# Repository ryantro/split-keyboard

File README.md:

# split-keyboard

I chose this as my project for [ECE 561 - Hardware/Software Design of Embedded Systems](https://www.online.colostate.edu/courses/ECE/ECE561.dot)

The project is a split mechanical keyboard built from scratch (and a microprocessor development board).

The noteable features:
- Split halves: Communicate via an I2C bus. The left half is the master device and the left half is the slave device.
- Profile selection: Special keys change the profile of the keyboard, changing the functions of certain keys and the joystick.
- LCD screen: Indicates the currently active profile.
- Joystick: Can act as either a mouse or a joystick depending on profile.

# Tools

### KiCAD

Schematic and PCB layout designed in KiCAD.

PCBs ordered from [https://www.pcbway.com/](https://www.pcbway.com/)

### Teensyduino

Firmware written in Teensyduino IDE.

# Refrences

[https://github.com/ruiqimao/keyboard-pcb-guide](https://github.com/ruiqimao/keyboard-pcb-guide)

[https://www.pjrc.com/teensy/teensyduino.html](https://www.pjrc.com/teensy/teensyduino.html)

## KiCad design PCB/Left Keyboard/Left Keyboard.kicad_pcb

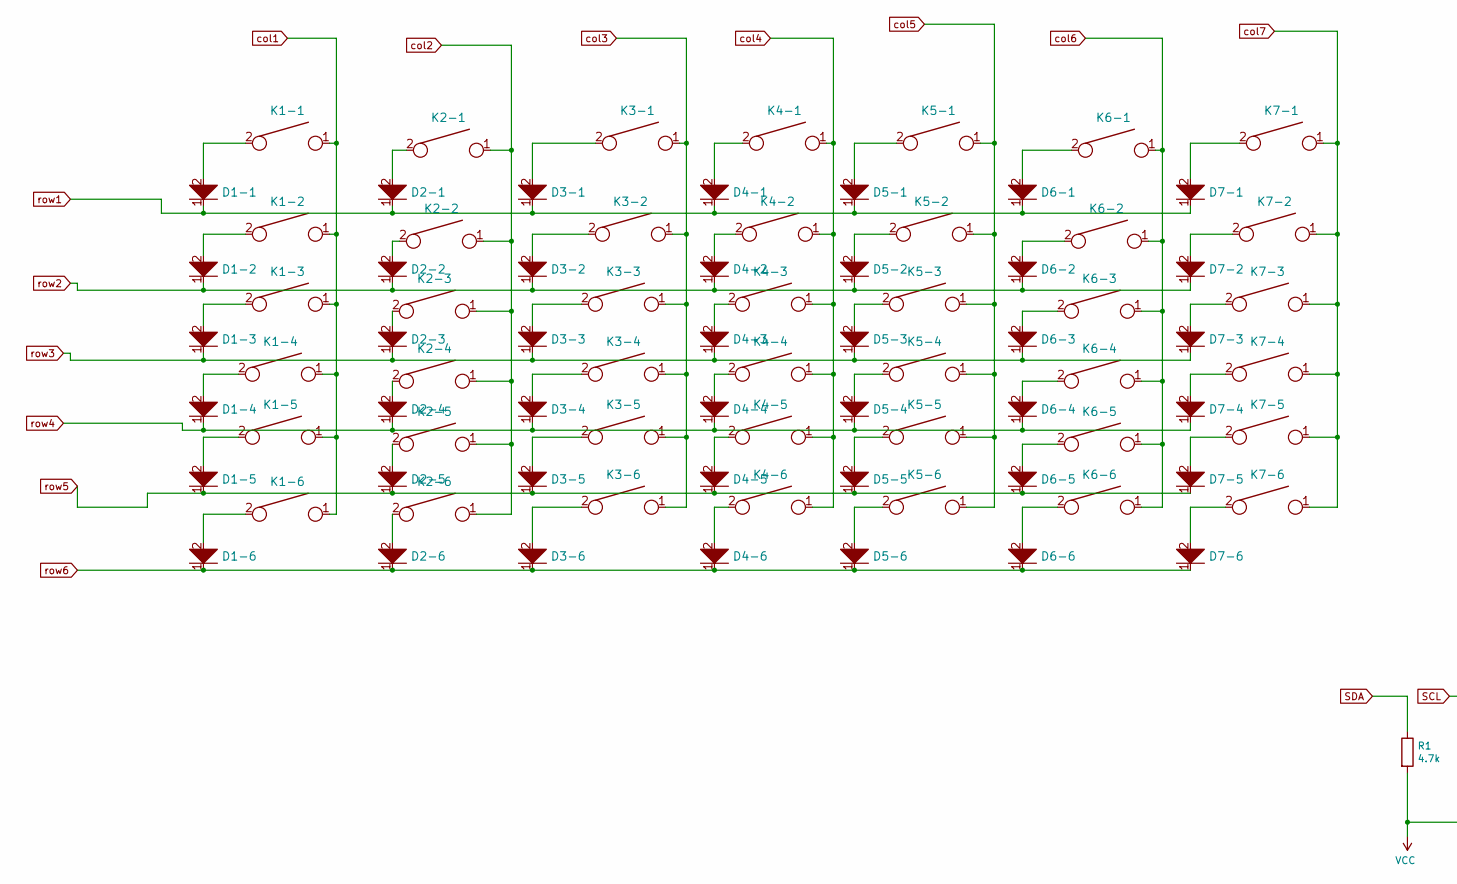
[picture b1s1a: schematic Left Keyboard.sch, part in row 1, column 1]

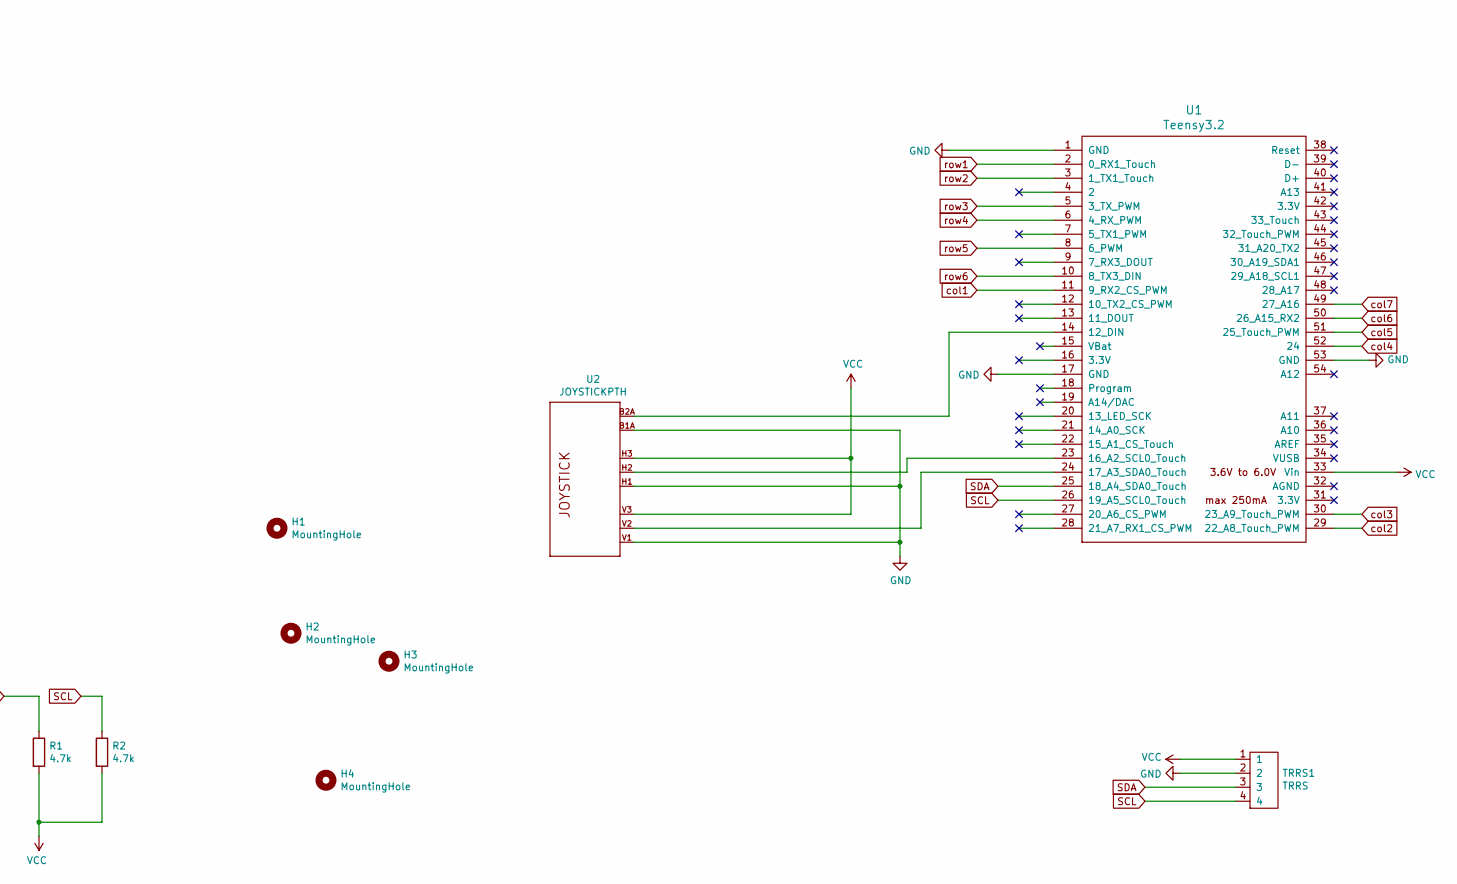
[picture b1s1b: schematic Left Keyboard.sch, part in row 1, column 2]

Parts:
D1-1, D1-2, D1-3, D1-4, D1-5, D1-6, D2-1, D2-2, D2-3, D2-4, D2-5, D2-6, D3-1, D3-2, D3-3, D3-4, D3-5, D3-6, D4-1, D4-2, D4-3, D4-4, D4-5, D4-6, D5-1, D5-2, D5-3, D5-4, D5-5, D5-6, D6-1, D6-2, D6-3, D6-4, D6-5, D6-6, D7-1, D7-2, D7-3, D7-4, D7-5, D7-6: D; D_axial
H1, H2, H3, H4: MountingHole; MountingHole_2.7mm_M2.5_Pad
K1-1, K1-2, K1-3, K1-4, K1-5, K1-6, K2-1, K2-2, K2-3, K2-4, K2-5, K2-6, K3-1, K3-2, K3-3, K3-4, K3-5, K3-6, K4-1, K4-2, K4-3, K4-4, K4-5, K4-6, K5-1, K5-2, K5-3, K5-4, K5-5, K5-6, K6-1, K6-2, K6-3, K6-4, K6-5, K6-6, K7-1, K7-2, K7-3, K7-4, K7-5, K7-6: KEYSW; Mx_Alps_100
R1, R2: 4.7k; R_Axial_DIN0207_L6.3mm_D2.5mm_P7.62mm_Horizontal
TRRS1: TRRS; TRRS-PJ-320A
U1: Teensy3.2; Teensy30_31_32_All_Pins
U2: JOYSTICKPTH; JOYSTICK

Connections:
GND: TRRS1.2, U1.1 (GND), U1.17 (GND), U1.53 (GND), U2.B1A (SEL+), U2.H1 (H+), U2.V1 (V+)
unnamed: D1-1.2, K1-1.2
unnamed: D1-2.2, K1-2.2
unnamed: D1-3.2, K1-3.2
unnamed: D1-4.2, K1-4.2
unnamed: D1-5.2, K1-5.2
unnamed: D1-6.2, K1-6.2
unnamed: D2-1.2, K2-1.2
unnamed: D2-2.2, K2-2.2
unnamed: D2-3.2, K2-3.2
unnamed: D2-4.2, K2-4.2
unnamed: D2-5.2, K2-5.2
unnamed: D2-6.2, K2-6.2
unnamed: D3-1.2, K3-1.2
unnamed: D3-2.2, K3-2.2
unnamed: D3-3.2, K3-3.2
unnamed: D3-4.2, K3-4.2
unnamed: D3-5.2, K3-5.2
unnamed: D3-6.2, K3-6.2
unnamed: D4-1.2, K4-1.2
unnamed: D4-2.2, K4-2.2
unnamed: D4-3.2, K4-3.2
unnamed: D4-4.2, K4-4.2
unnamed: D4-5.2, K4-5.2
unnamed: D4-6.2, K4-6.2
unnamed: D5-1.2, K5-1.2
unnamed: D5-2.2, K5-2.2
unnamed: D5-3.2, K5-3.2
unnamed: D5-4.2, K5-4.2
unnamed: D5-5.2, K5-5.2
unnamed: D5-6.2, K5-6.2
unnamed: D6-1.2, K6-1.2
unnamed: D6-2.2, K6-2.2
unnamed: D6-3.2, K6-3.2
unnamed: D6-4.2, K6-4.2
unnamed: D6-5.2, K6-5.2
unnamed: D6-6.2, K6-6.2
unnamed: D7-1.2, K7-1.2
unnamed: D7-2.2, K7-2.2
unnamed: D7-3.2, K7-3.2
unnamed: D7-4.2, K7-4.2
unnamed: D7-5.2, K7-5.2
unnamed: D7-6.2, K7-6.2
unnamed: U1.14 (12_DIN), U2.B2A (SEL-)
unnamed: U1.23 (16_A2_SCL0_Touch), U2.H2 (H)
unnamed: U1.24 (17_A3_SDA0_Touch), U2.V2 (V)
SCL: R2.1, TRRS1.4, U1.26 (19_A5_SCL0_Touch)
SDA: R1.1, TRRS1.3, U1.25 (18_A4_SDA0_Touch)
VCC: R1.2, R2.2, TRRS1.1, U1.33 (Vin), U2.H3 (H-), U2.V3 (V-)
col1: K1-1.1, K1-2.1, K1-3.1, K1-4.1, K1-5.1, K1-6.1, U1.11 (9_RX2_CS_PWM)
col2: K2-1.1, K2-2.1, K2-3.1, K2-4.1, K2-5.1, K2-6.1, U1.29 (22_A8_Touch_PWM)
col3: K3-1.1, K3-2.1, K3-3.1, K3-4.1, K3-5.1, K3-6.1, U1.30 (23_A9_Touch_PWM)
col4: K4-1.1, K4-2.1, K4-3.1, K4-4.1, K4-5.1, K4-6.1, U1.52 (24)
col5: K5-1.1, K5-2.1, K5-3.1, K5-4.1, K5-5.1, K5-6.1, U1.51 (25_Touch_PWM)
col6: K6-1.1, K6-2.1, K6-3.1, K6-4.1, K6-5.1, K6-6.1, U1.50 (26_A15_RX2)
col7: K7-1.1, K7-2.1, K7-3.1, K7-4.1, K7-5.1, K7-6.1, U1.49 (27_A16)
row1: D1-1.1, D2-1.1, D3-1.1, D4-1.1, D5-1.1, D6-1.1, D7-1.1, U1.2 (0_RX1_Touch)
row2: D1-2.1, D2-2.1, D3-2.1, D4-2.1, D5-2.1, D6-2.1, D7-2.1, U1.3 (1_TX1_Touch)
row3: D1-3.1, D2-3.1, D3-3.1, D4-3.1, D5-3.1, D6-3.1, D7-3.1, U1.5 (3_TX_PWM)
row4: D1-4.1, D2-4.1, D3-4.1, D4-4.1, D5-4.1, D6-4.1, D7-4.1, U1.6 (4_RX_PWM)
row5: D1-5.1, D2-5.1, D3-5.1, D4-5.1, D5-5.1, D6-5.1, D7-5.1, U1.8 (6_PWM)
row6: D1-6.1, D2-6.1, D3-6.1, D4-6.1, D5-6.1, D6-6.1, D7-6.1, U1.10 (8_TX3_DIN)

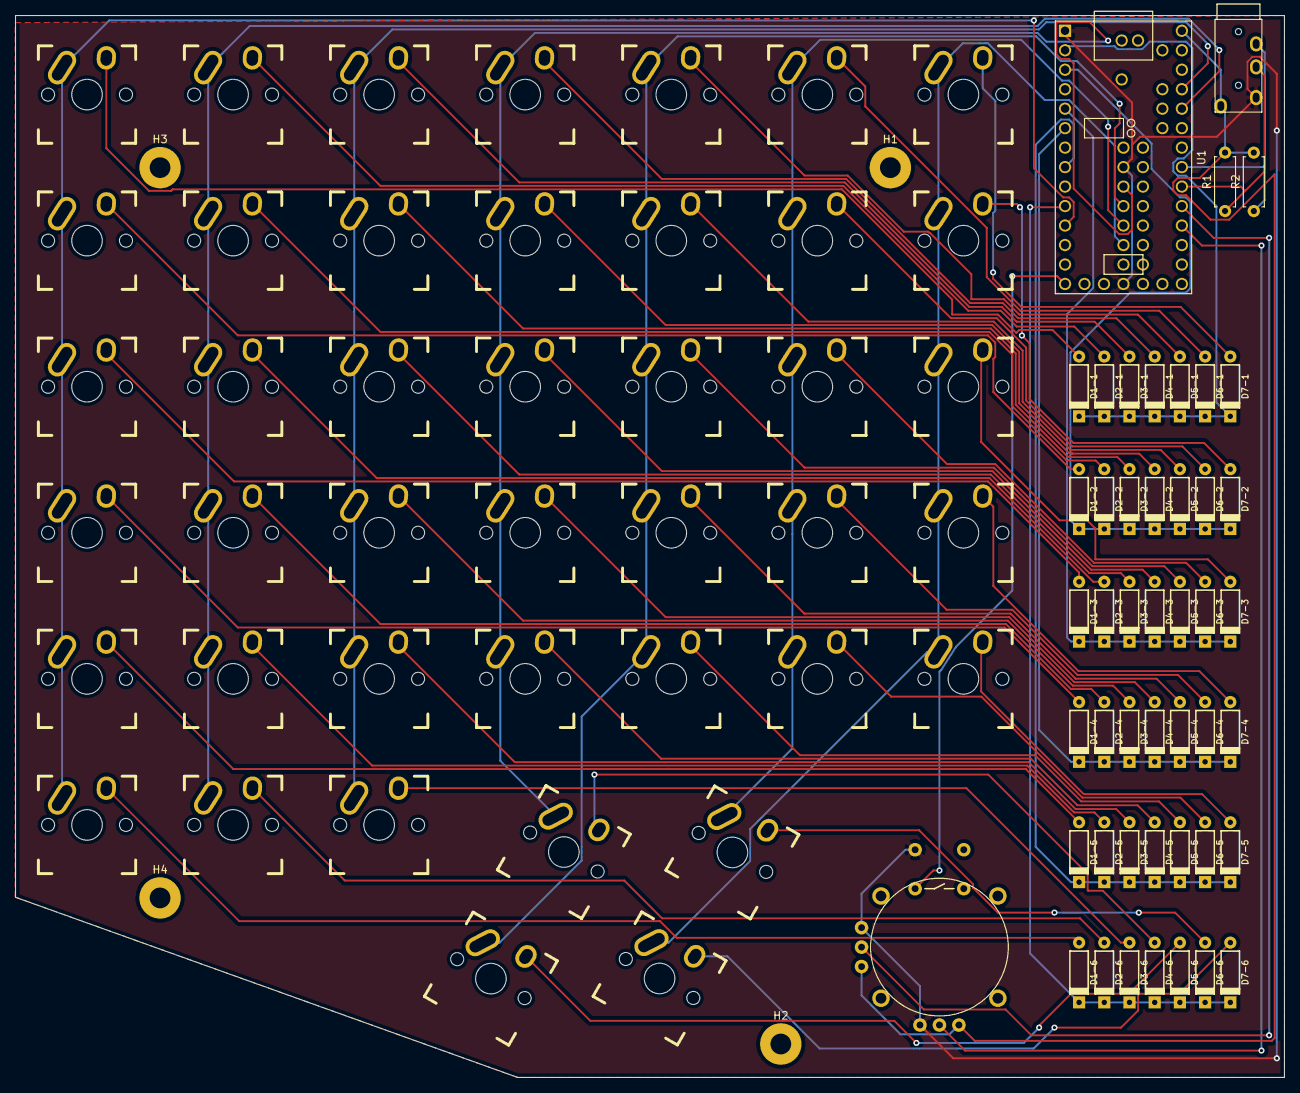
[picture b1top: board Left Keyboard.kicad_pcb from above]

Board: 2 copper layers, 165.5 x 138.5 mm, 93 parts (0 on the bottom side), 62 nets.

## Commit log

2021-08-16 edit
